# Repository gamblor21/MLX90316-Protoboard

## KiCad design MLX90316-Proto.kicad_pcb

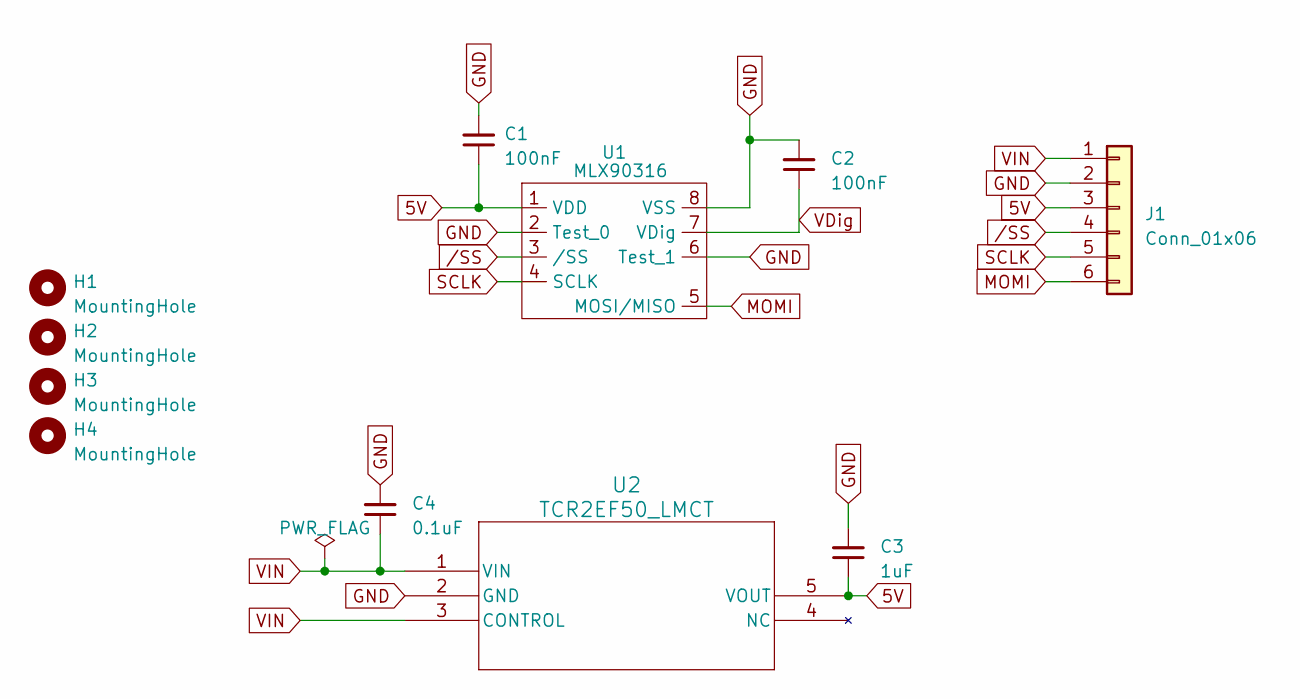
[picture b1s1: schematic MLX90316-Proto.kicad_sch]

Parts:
C1, C2: 100nF; C_0805_2012Metric
C3: 1uF; C_0805_2012Metric
C4: 0.1uF; C_0805_2012Metric
H1, H2, H3, H4: MountingHole; MountingHole_2.7mm_M2.5
J1: Conn_01x06; PinHeader_1x06_P2.54mm_Vertical
U1: MLX90316; SOIC-8_3.9x4.9mm_P1.27mm
U2: TCR2EF50_LMCT; SOT_EF50_LMCT_TOS

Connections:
5V: C1.1, C3.1, J1.3, U1.1 (VDD), U2.5 (VOUT)
GND: C1.2, C2.2, C3.2, C4.2, J1.2, U1.2 (Test_0), U1.6 (Test_1), U1.8 (VSS), U2.2 (GND)
MOMI: J1.6, U1.5 (MOSI/MISO)
SCLK: J1.5, U1.4 (SCLK)
VDig: C2.1, U1.7 (VDig)
VIN: C4.1, J1.1, U2.1 (VIN), U2.3 (CONTROL)
/SS: J1.4, U1.3 (/SS)

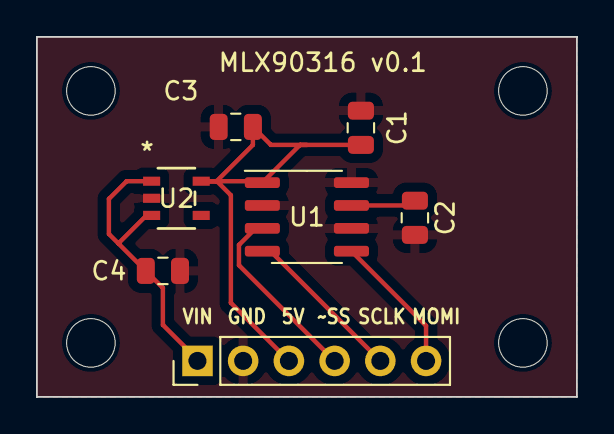
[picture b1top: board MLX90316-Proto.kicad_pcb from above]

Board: 2 copper layers, 30.0 x 20.0 mm, 11 parts (0 on the bottom side), 7 nets.
